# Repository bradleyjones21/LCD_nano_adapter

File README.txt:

This project is a simple LCD to arduino nano converter for easy setup and use of an LCD.
Work done in KiCAD.

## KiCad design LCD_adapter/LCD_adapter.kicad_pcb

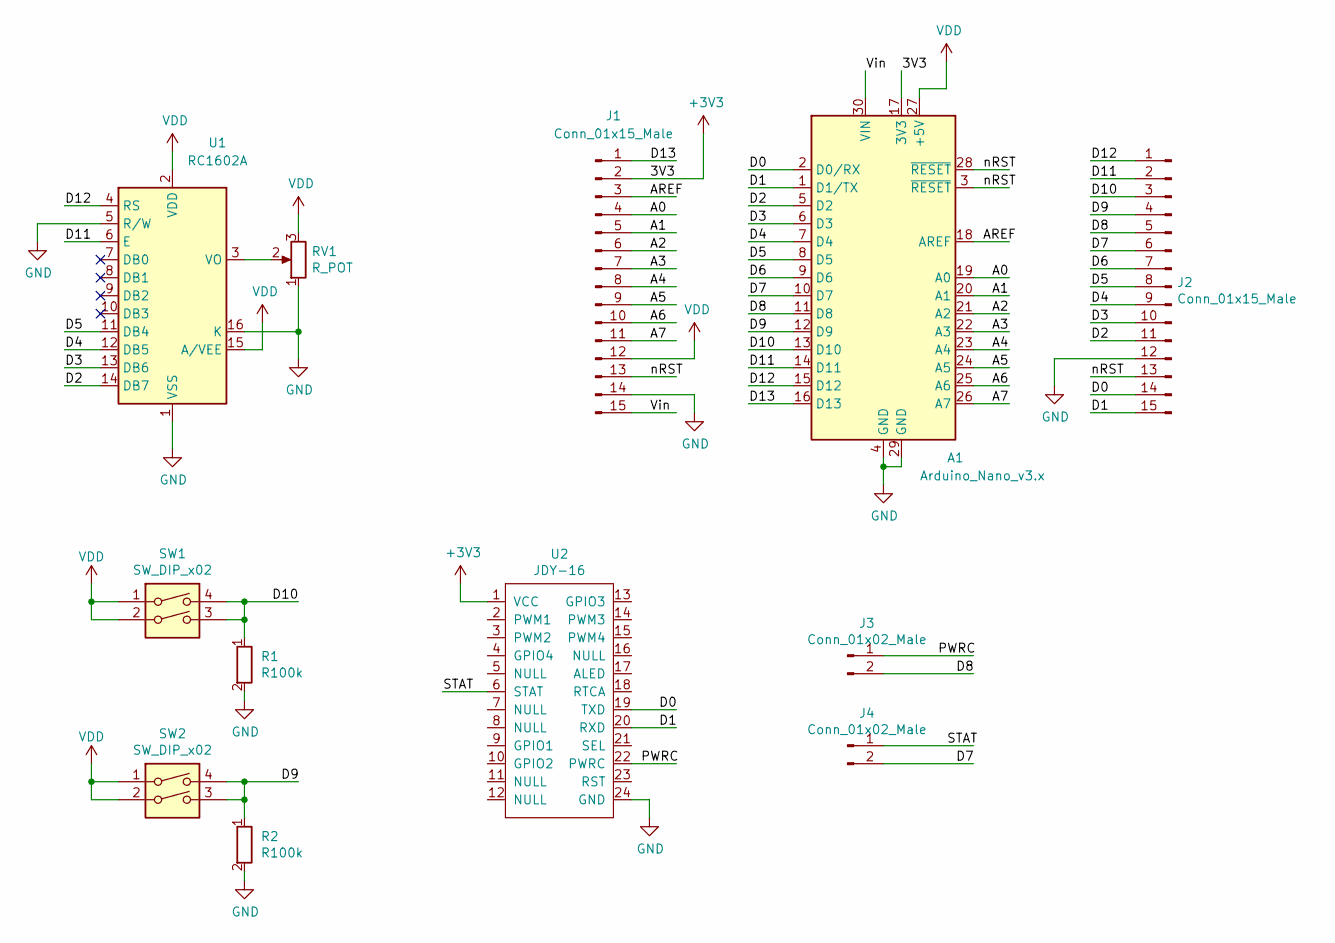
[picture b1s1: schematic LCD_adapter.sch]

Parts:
A1: Arduino_Nano_v3.x; Arduino_Nano
J1, J2: Conn_01x15_Male; PinHeader_1x15_P2.54mm_Vertical
J3, J4: Conn_01x02_Male; PinHeader_1x02_P2.54mm_Vertical
R1, R2: R100k; R_Axial_DIN0207_L6.3mm_D2.5mm_P7.62mm_Horizontal
RV1: R_POT; Potentiometer
SW1, SW2: SW_DIP_x02; SW_PUSH_6mm_H9.5mm
U1: RC1602A; PinHeader_1x16_P2.54mm_Vertical
U2: JDY-16

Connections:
+3V3: A1.17 (3V3), J1.2, U2.1 (VCC)
/A0: A1.19 (A0), J1.4
/A1: A1.20 (A1), J1.5
/A2: A1.21 (A2), J1.6
/A3: A1.22 (A3), J1.7
/A4: A1.23 (A4), J1.8
/A5: A1.24 (A5), J1.9
/A6: A1.25 (A6), J1.10
/A7: A1.26 (A7), J1.11
/AREF: A1.18 (AREF), J1.3
/D0: A1.2 (D0/RX), J2.14, U2.19 (TXD)
/D1: A1.1 (D1/TX), J2.15, U2.20 (RXD)
/D2: A1.5 (D2), J2.11, U1.14 (DB7)
/D3: A1.6 (D3), J2.10, U1.13 (DB6)
/D4: A1.7 (D4), J2.9, U1.12 (DB5)
/D5: A1.8 (D5), J2.8, U1.11 (DB4)
/D6: A1.9 (D6), J2.7
/D7: A1.10 (D7), J2.6, J4.2
/D8: A1.11 (D8), J2.5, J3.2
/D9: A1.12 (D9), J2.4, R2.1, SW2.3, SW2.4
/D10: A1.13 (D10), J2.3, R1.1, SW1.3, SW1.4
/D11: A1.14 (D11), J2.2, U1.6 (E)
/D12: A1.15 (D12), J2.1, U1.4 (RS)
/D13: A1.16 (D13), J1.1
/PWRC: J3.1, U2.22 (PWRC)
/STAT: J4.1, U2.6 (STAT)
/Vin: A1.30 (VIN), J1.15
/nRST: A1.3 (~RESET), A1.28 (~RESET), J1.13, J2.13
GND: A1.4 (GND), A1.29 (GND), J1.14, J2.12, R1.2, R2.2, RV1.1, U1.1 (VSS), U1.5 (R/W), U1.16 (K), U2.24 (GND)
unnamed: RV1.2, U1.3 (VO)
VDD: A1.27 (+5V), J1.12, RV1.3, SW1.1, SW1.2, SW2.1, SW2.2, U1.2 (VDD), U1.15 (A/VEE)

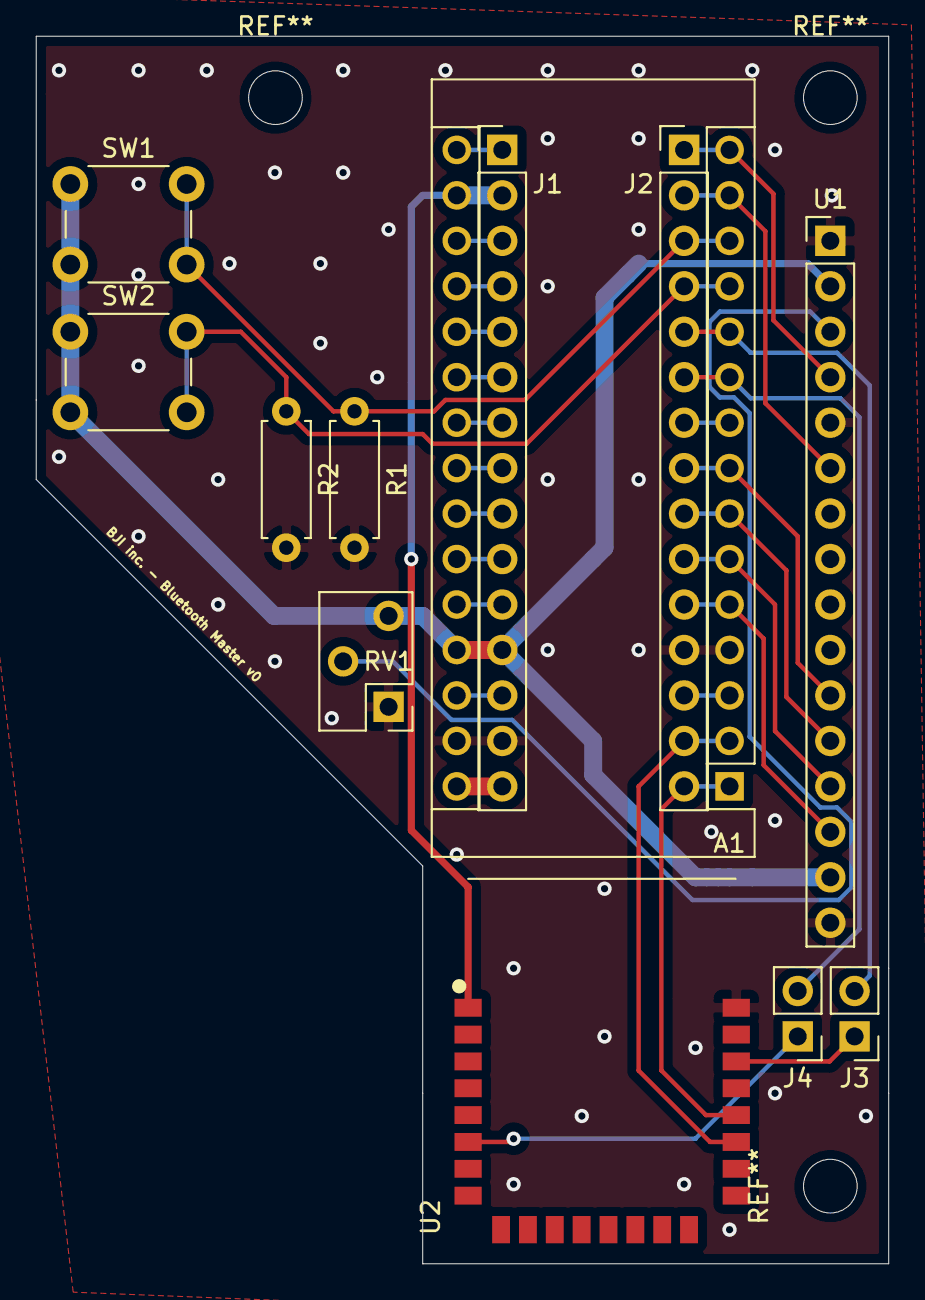
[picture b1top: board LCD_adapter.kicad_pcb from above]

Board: 2 copper layers, 47.6 x 68.6 mm, 12 parts (0 on the bottom side), 31 nets.

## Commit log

2022-01-06 init design
2022-01-07 version 1 complete
2022-01-08 updated gerbers
2022-01-09 bluetooth module v0 - updated to include the bluetooth module and buttons for control
2022-01-11 fixed for DRC errors
2022-03-11 Added images and readme
